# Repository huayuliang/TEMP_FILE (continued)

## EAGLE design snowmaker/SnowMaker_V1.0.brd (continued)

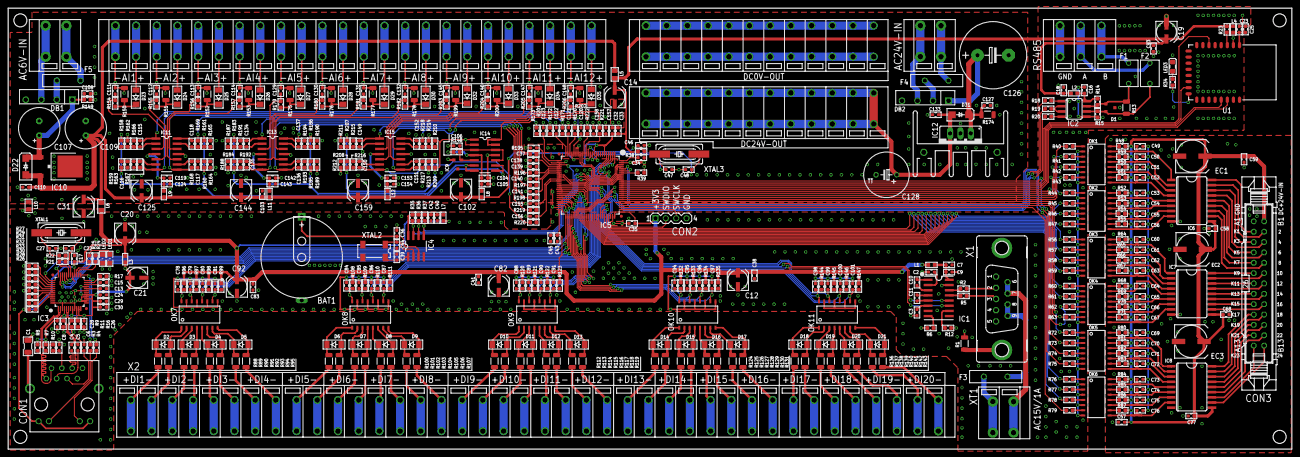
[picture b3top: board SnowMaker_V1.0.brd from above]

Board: 2 copper layers, 315.0 x 108.2 mm, 571 parts (0 on the bottom side), 406 nets.

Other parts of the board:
U$1: SNOWMAKER_V1_OUTLINE

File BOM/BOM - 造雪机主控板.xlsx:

| 造雪机主控板 |  |  |  | 编制 | 花玉良 |  | 产品编号
 |  |  |  |  | 版本 | V1 |  | 产品名称
 |  |  |  |  | 日期 | 43020 |  | 产品型号 | SMMB
 |  |  |  |  | 客户
内部编号 | 零件名称 | 元件代号 | 型号、规格 | 封装 | 数量 | 单位 | 品牌 | 单价 | 备注
焊接物料 |  |  |  |  | 1 | 套
 | 表贴元件
 | 贴片多层陶瓷电容 | C1 | 1nF/2kV | C1206 | 1 | 个
 | 贴片多层陶瓷电容 | C4、C5 | 6.8nF/50V | C0603 | 2 | 个
 | 贴片多层陶瓷电容 | C8 | 22nF/50V | C0603 | 1 | 个
 | 贴片多层陶瓷电容 | C39、C44 | 6.8pF/50V/NP0 | C0603 | 2 | 个
 | 贴片多层陶瓷电容 | C27、C22、C47、C48 | 18pF/50V/NP0 | C0603 | 4 | 个
 | 贴片多层陶瓷电容 | C115、C116、C117、C118、C134、C135、C136、C137、C149、C150、C151、C152 | 30pF/50V | C0603 | 12 | 个
 | 贴片多层陶瓷电容 | C120、C121、C122、C123、C138、C139、C140、C141、C155、C156、C157、C158 | 1nF/50V | C0603 | 12 | 个
 | 贴片多层陶瓷电容 | C6、C15、C49、C50、C51、C52、C53、C54、C55、C56、C60、C61、C62、C63、C64、C65、C66、C67、C69、C70、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 | 10nF/50V | C0603 | 49 | 个
 | 贴片多层陶瓷电容 | C2、C3、C9、C10、C11、C16、C17、C18、C24、C25、C26、C28、C29、C32、C33、C34、C35、C36、C37、C38、C4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 | 100nF/50V | C0603 | 51 | 个
 | 贴片多层陶瓷电容 | C13 | 4.7uF/10V | C0603 | 1 | 个
 | 贴片多层陶瓷电容 | C7、C23、C30、C42、C105、C124、C154、C143 | 10uF/16V | C0603 | 8 | 个
 | 贴片铝电解 5X5 | C102、C144、C159、C125 | 47uF/6.3V 5x5.8 | UD-5X5,8_NICHICON | 4 | 个
 | 贴片铝电解 5X5 | C14、C12、C19、C20、C21、C31、C82、C92 | 100uF/6.3V 5x5.8 | UD-5X5,8_NICHICON | 8 | 个
 | 贴片铝电解 8X10 | EC1、EC2、EC3 | 220uF/50V | UD-8X10_NICHICON | 3 | 个
 | 贴片电阻 | R1、R18、R19、R20、R22 | 0R | R1206 | 5 | 个
 | 贴片电阻 | R10 | 10R | R0603 | 1 | 个
 | 贴片电阻 | R2、R5 | 22R | R0603 | 2 | 个
 | 贴片电阻 | R7、R8、R9、R11 | 49R9 | R0603 | 4 | 个
 | 贴片电阻 | R14、R15 | 2.4k | R0603 | 2 | 个
 | 贴片电阻 | R16 | 12.4k/1% | R0603 | 1 | 个
 | 贴片电阻 | R21 | 1M | R0603 | 1 | 个
 | 贴片电阻 | R3、R4、R24、R25、R40、R41、R42、R43、R44、R45、R46、R47、R56、R57、R58、R59、R60、R61、R62、R63、R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 | 330R | R0603 | 11 | 个
 | 贴片电阻 | R34、R170、R171、R172、R173、R195、R196、R197、R198、R219、R220、R221、R222 | 1k | R0603 | 13 | 个
 | 贴片电阻 | R88、R89、R90、R91、R92、R93、R94、R95、R100、R101、R102、R103、R104、R105、R106、R107、R112、R1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 | 2.2k | R1206 | 40 | 个
 | 贴片电阻 | R6、R17、R12、R23、R26、R27、R28、R29、R30、R31、R32、R33、R35、R36、R37、R38、R39、R96、R97、R98、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 | 10k | R0603 | 51 | 个
 | 贴片电阻 | R48、R49、R50、R51、R52、R53、R54、R55、R64、R65、R66、R67、R68、R69、R70、R71、R80、R81、R82、R83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 | 20K | R0603 | 25 | 个
 | 贴片电阻 | R13 | 120R | R1206 | 1 | 个
 | 贴片电阻 | R150、R151、R152、R153、R175、R176、R177、R178、R199、R200、R201、R202 | 120R/0.1% | R1206 | 12 | 个
 | 贴片电阻 | R158、R159、R160、R161、R183、R184、R185、R186、R207、R208、R209、R210 | 5.11k/1% | R0603 | 12 | 个
 | 贴片电阻 | R166、R167、R168、R169、R191、R192、R193、R194、R215、R216、R217、R218 | 1k/1% | R0603 | 12 | 个
 | 贴片电阻 | R162、R163、R164、R165、R187、R188、R189、R190、R211、R212、R213、R214 | 124k/1% | R0603 | 12 | 个
 | 贴片磁珠 | L1、L2、L3、L4、L7 | 600R/100MHz | L0603 | 5 | 个
 | 贴片磁珠 | L5、L6、L10 | 100R/100MHz | L0805 | 3 | 个
 | 贴片电感 | L8、L9、L11、L12 | 10uH | L0603 | 4 | 个
 | 0805 贴片 LED | LED1 | 红色 0805 LED | LED0805 | 1 | 个
 |  | LED2、LED3 | 绿色 0805 LED | LED0805 | 2 | 个
 | 晶振 | XTAL1 | 25MHz | SM49 | 1 | 个
 | 晶振 | XTAL2 | MC-306 32.768000kHz 12.5 +20.0-20.0 | MC306 | 1 | 个
 | 晶振 | XTAL3 | 8MHz | SM49 | 1 | 个
 | TVS 管 | D1 | SM712-02H | SOT23-3 | 1 | 个
 | 开关二极管 | D2、D3、D4、D5、D6、D7、D8、D9、D10、D11、D12、D13、D14、D15、D16、D17、D18、D19、D20、D21、D23、D24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 | 1N4148 | MINI_MELF(LL-34) | 32 | 个
 | 整流二极管 | D22、D31 | 1N4007 | SMA-DO214AC | 2 | 个
 | 贴片整流桥 | DB2 | KBP2005G | KBP2005 | 1 | 个
 | 四通道光耦 | OK1、OK2、OK3、OK4、OK5、OK6、OK7、OK8、OK9、OK10、OK11 | TLP283-4 | MINI-FLAT-16 | 11 | 个
 | RS232 收发 IC | IC1 | ST3232BD | SO16 | 1 | 个
 | RS485 收发 IC | IC2 | ST3485EBD | SO08 | 1 | 个
 | 以太网 IC | IC3 | W5500 | LQFP48_7X7_0.5P | 1 | 个
 | 实时时钟 IC | IC4 | SD2068 | SOIC-8 | 1 | 个
 | MCU | IC5 | STM32F103VCT6 | LQFP100_14X14MM | 1 | 个
 | 多路达林顿驱动IC | IC6、IC7、IC8 | ULN2803 | SO18W | 3 | 个
 | 基准电压源IC | IC9 | LM4040AIM3X-2.5 | SOT23-3 | 1 | 个
 | 3.3V稳压IC | IC10 | LM1117IDTX-3.3 | TO-252/DPAK | 1 | 个
 | R2R 四运放 | IC11、IC13、IC14、IC15 | SGM8584XS14 | SOIC-14 | 4 | 个
 | 蓝牙模块 | U1 | LQ-BTM2540 | LQ-BTM2540 | 1 | 个 | 蓝讯科技
 |  |  |  |  |  | 个
 | 直插元件
 | 24V 线性稳压IC | IC12 | LM78M24 | TO-220 | 1 | 个
 | 直插铝电解电容 | C109 | 220uF/16V_M10*16 | E3 | 1 | 个
 | 直插铝电解电容 | C107 | 1000uF/16V_M10*16 | E3 | 1 | 个
 | 直插铝电解电容 | C128 | 1000uF/35V_M10*16 | E3 | 1 | 个
 | 直插铝电解电容 | C126 | 2200uF/50V_M16*25 | E7 | 1 | 个
 | 120mA PPTC 保险丝 | F1、F2 | TRF250-120T |  | 2 | 个
 | 1A PPTC 保险丝 | F3、F4、F5 | RXEF110 |  | 3 | 个
 | TO-220 散热器（含螺丝） | HS1 | 23mm * 16.5mm * 30mm |  | 1 | 套
 | 电池 | BAT1 | CR2032/1HF | CR2032-HF | 1 | 个
 | 带变压器 RJ45 座 | CON1 | HR951180A |  | 1 | 个
 | 4Pin 排针 | CON2 | 4Pin 2.54mm 单排针 | PH2.54-4P | 1 | 个
 | 26Pin 牛角座 | CON3 | 26Pin 牛角座 | 26V | 1 | 个
 | DB9 母座 | X1 | SUB-D 母座 9P 180度 | F09VP | 1 | 个
 | 2Pin 绿色弹簧端子 | XT1、XT3、XT4 | FFKDS/V1-5.08-2 | FFKDS/V1-5.08-2 | 3 | 个
 | 2Pin 绿色弹簧端子 | XT2 | FFKDS/V1-5.08-3 | FFKDS/V1-5.08-3 | 1 | 个
 | 2Pin 绿色弹簧端子 |  | FFKDS/V1-5.08-24 | FFKDS/V1-5.08-24 | 1 | 个
 | 2Pin 绿色弹簧端子 |  | FFKDS/V1-5.08-12 | FFKDS/V1-5.08-12 | 2 | 个
 | 2Pin 绿色弹簧端子 |  | FFKDS/V1-5.08-40 | FFKDS/V1-5.08-40 | 1 | 个
组装物料 |  |  |  |  | 1 | 套
 | PCB | SMMB | 315mm*100mm |  | 1 | 个
70607030 | 自攻螺丝 |  | M3X16 |  | 3 | 个
70105006 | 绿色底板 |  | 宽度108.2mm 长315-2-2mm |  | 0.311 | 米
70608009 | 挡片(左) |  | 宽度108.2mm |  | 1 | 个
70608010 | 挡片(右) |  | 宽度108.2mm |  | 1 | 个
 | 控制变压器（需定制） |  | 输入电压：220V/380V；输出：绕组 1：5V/1A；绕组 2：24V/1.2A；绕组3：12V/1.2A |  | 1 | 个
 | 蓝牙天线及转接线 |  |  |  | 1 | 套 | 蓝讯科技
指定蓝讯科技
蓝牙模块链接：https://item.taobao.com/item.htm?spm=a1z10.3-c.w4002-1228054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
蓝牙天线及转接线链接：https://item.taobao.com/item.htm?spm=2013.1.0.0.412946db8S2J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
变压器不限厂家
变压器定制链接：https://item.taobao.com/item.htm?spm=a1z0d.7625083.199830226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

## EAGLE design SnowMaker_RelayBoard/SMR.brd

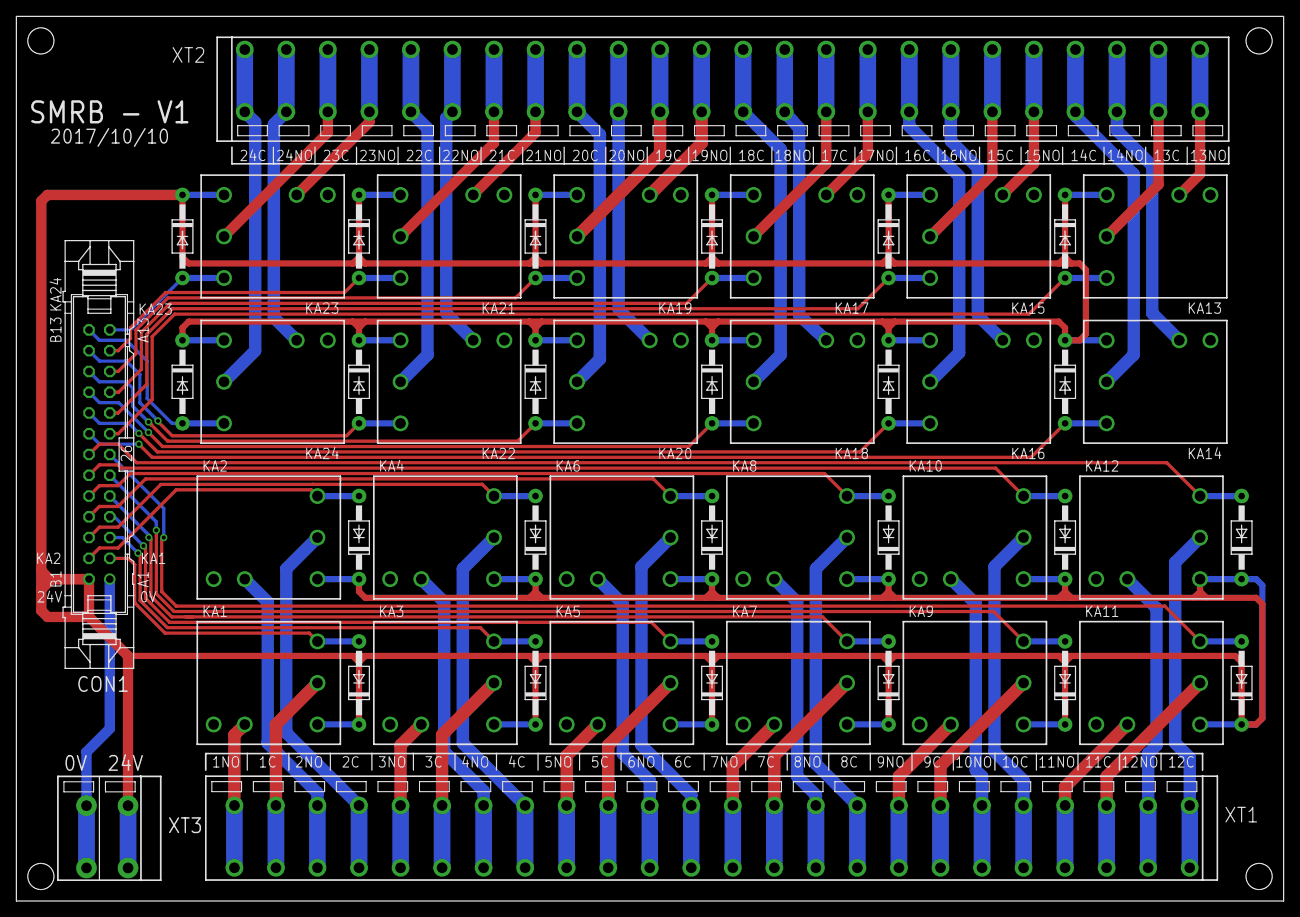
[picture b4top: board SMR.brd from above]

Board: 2 copper layers, 155.0 x 108.2 mm, 54 parts (0 on the bottom side), 74 nets.

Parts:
CON1: CON-HARTING-26V; 26V
D1, D2, D3, D4, D5, D6, D7, D8, D9, D10, D11, D12, D13, D14, D15, D16, D17, D18, D19, D20, D21, D22, D23, D24: 1N4007; DO41-10
KA1, KA2, KA3, KA4, KA5, KA6, KA7, KA8, KA9, KA10, KA11, KA12, KA13, KA14, KA15, KA16, KA17, KA18, KA19, KA20, KA21, KA22, KA23, KA24: HFKM-024-1ZST; HFKM-1ZST
LOGO1: SY-LOGO_BOTTOM
U$1: 108.2-OUTLINE
XT1, XT2: FFKDS/V1-5.08-24
XT3: FFKDS/V1-5.08-2

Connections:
+24V: CON1.B1, D1.C, D2.C, D3.C, D4.C, D5.C, D6.C, D7.C, D8.C, D9.C, D10.C, D11.C, D12.C, D13.C, D14.C, D15.C, D16.C, D17.C, D18.C, D19.C, D20.C, D21.C, D22.C, D23.C, D24.C, KA1.1, KA2.1, KA3.1, KA4.1, KA5.1, KA6.1, KA7.1, KA8.1, KA9.1, KA10.1, KA11.1, KA12.1, KA13.1, KA14.1, KA15.1, KA16.1, KA17.1, KA18.1, KA19.1, KA20.1, KA21.1, KA22.1, KA23.1, KA24.1, XT3.2@1, XT3.2@2
GND1: CON1.A1, XT3.1@1, XT3.1@2
KA1: CON1.A2, D1.A, KA1.2
KA2: CON1.B2, D2.A, KA2.2
KA3: CON1.A3, D3.A, KA3.2
KA4: CON1.B3, D4.A, KA4.2
KA5: CON1.A4, D5.A, KA5.2
KA6: CON1.B4, D6.A, KA6.2
KA7: CON1.A5, D7.A, KA7.2
KA8: CON1.B5, D8.A, KA8.2
KA9: CON1.A6, D9.A, KA9.2
KA10: CON1.B6, D10.A, KA10.2
KA11: CON1.A7, D11.A, KA11.2
KA12: CON1.B7, D12.A, KA12.2
KA13: CON1.A8, D13.A, KA13.2
KA14: CON1.B8, D14.A, KA14.2
KA15: CON1.A9, D15.A, KA15.2
KA16: CON1.B9, D16.A, KA16.2
KA17: CON1.A10, D17.A, KA17.2
KA18: CON1.B10, D18.A, KA18.2
KA19: CON1.A11, D19.A, KA19.2
KA20: CON1.B11, D20.A, KA20.2
KA21: CON1.A12, D21.A, KA21.2
KA22: CON1.B12, D22.A, KA22.2
KA23: CON1.A13, D23.A, KA23.2
KA24: CON1.B13, D24.A, KA24.2
unnamed: KA1.4, XT1.1@2, XT1.2@2
unnamed: KA1.5, XT1.1@1, XT1.2@1
unnamed: KA3.4, XT1.1@6, XT1.2@6
unnamed: KA3.5, XT1.1@5, XT1.2@5
unnamed: KA8.5, XT1.1@15, XT1.2@15
unnamed: KA8.4, XT1.1@16, XT1.2@16
unnamed: KA7.5, XT1.1@13, XT1.2@13
unnamed: KA7.4, XT1.1@14, XT1.2@14
unnamed: KA6.5, XT1.1@11, XT1.2@11
unnamed: KA6.4, XT1.1@12, XT1.2@12
unnamed: KA5.5, XT1.1@9, XT1.2@9
unnamed: KA5.4, XT1.1@10, XT1.2@10
unnamed: KA4.5, XT1.1@7, XT1.2@7
unnamed: KA4.4, XT1.1@8, XT1.2@8
unnamed: KA2.5, XT1.1@3, XT1.2@3
unnamed: KA2.4, XT1.1@4, XT1.2@4
unnamed: KA9.4, XT1.1@18, XT1.2@18
unnamed: KA9.5, XT1.1@17, XT1.2@17
unnamed: KA16.5, XT2.1@7, XT2.2@7
unnamed: KA16.4, XT2.1@8, XT2.2@8
unnamed: KA15.5, XT2.1@5, XT2.2@5
unnamed: KA15.4, XT2.1@6, XT2.2@6
unnamed: KA14.5, XT2.1@3, XT2.2@3
unnamed: KA14.4, XT2.1@4, XT2.2@4
unnamed: KA13.5, XT2.1@1, XT2.2@1
unnamed: KA13.4, XT2.1@2, XT2.2@2
unnamed: KA12.5, XT1.1@23, XT1.2@23
unnamed: KA12.4, XT1.1@24, XT1.2@24
unnamed: KA11.5, XT1.1@21, XT1.2@21
unnamed: KA11.4, XT1.1@22, XT1.2@22
unnamed: KA10.5, XT1.1@19, XT1.2@19
unnamed: KA10.4, XT1.1@20, XT1.2@20
unnamed: KA17.4, XT2.1@10, XT2.2@10
unnamed: KA17.5, XT2.1@9, XT2.2@9
unnamed: KA24.5, XT2.1@23, XT2.2@23
unnamed: KA24.4, XT2.1@24, XT2.2@24
unnamed: KA23.5, XT2.1@21, XT2.2@21
unnamed: KA23.4, XT2.1@22, XT2.2@22
unnamed: KA22.5, XT2.1@19, XT2.2@19
unnamed: KA22.4, XT2.1@20, XT2.2@20
unnamed: KA21.5, XT2.1@17, XT2.2@17
unnamed: KA21.4, XT2.1@18, XT2.2@18
unnamed: KA20.5, XT2.1@15, XT2.2@15
unnamed: KA20.4, XT2.1@16, XT2.2@16
unnamed: KA19.5, XT2.1@13, XT2.2@13
unnamed: KA19.4, XT2.1@14, XT2.2@14
unnamed: KA18.5, XT2.1@11, XT2.2@11
unnamed: KA18.4, XT2.1@12, XT2.2@12

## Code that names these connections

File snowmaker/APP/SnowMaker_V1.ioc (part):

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Mcu.Name=STM32F103V(C-D-E)Tx
Mcu.Package=LQFP100
Mcu.UserName=STM32F103VCTx
PA0-WKUP.Signal=ADCx_IN0
PA1.Signal=ADCx_IN1
PA10.GPIOParameters=GPIO_Label
PA10.GPIO_Label=TLCMP-RX
PA10.Mode=Asynchronous
PA10.Signal=USART1_RX
PA11.GPIOParameters=GPIO_Label
PA11.GPIO_Label=DOUT22
PA11.Signal=GPIO_Output
PA12.GPIOParameters=GPIO_Label
PA12.GPIO_Label=DOUT23
PA12.Signal=GPIO_Output
PA13.Mode=Serial_Wire
PA13.Signal=SYS_JTMS-SWDIO
PA14.Mode=Serial_Wire
PA14.Signal=SYS_JTCK-SWCLK
PA15.GPIOParameters=GPIO_Label
PA15.GPIO_Label=DOUT24
PA15.Signal=GPIO_Output
PA2.Signal=ADCx_IN2
PA3.Signal=ADCx_IN3
PA4.Signal=ADCx_IN4
PA5.Signal=ADCx_IN5
PA6.Signal=ADCx_IN6
PA7.Signal=ADCx_IN7
PA8.GPIOParameters=GPIO_Label
PA8.GPIO_Label=DOUT21
PA8.Signal=GPIO_Output
PA9.GPIOParameters=GPIO_Label
PA9.GPIO_Label=TLCMP-TX
PA9.Mode=Asynchronous
PA9.Signal=USART1_TX
PB0.Signal=ADCx_IN8
PB1.Signal=ADCx_IN9
PB10.GPIOParameters=GPIO_Label
PB10.GPIO_Label=ETH_INT
PB10.Signal=GPIO_Input
PB11.GPIOParameters=GPIO_Label
PB11.GPIO_Label=ETH_RST
PB11.Signal=GPIO_Output
PB12.GPIOParameters=GPIO_Label
PB12.GPIO_Label=ETHSPI_NSS
PB12.Mode=NSS_Signal_Hard_Output
PB12.Signal=SPI2_NSS
PB13.GPIOParameters=GPIO_Label
PB13.GPIO_Label=ETHSPI_SCK
PB13.Mode=Full_Duplex_Master
PB13.Signal=SPI2_SCK
PB14.GPIOParameters=GPIO_Label
PB14.GPIO_Label=ETHSPI_MISO
PB14.Mode=Full_Duplex_Master
PB14.Signal=SPI2_MISO
PB15.GPIOParameters=GPIO_Label
PB15.GPIO_Label=ETHSPI_MOSI
PB15.Mode=Full_Duplex_Master
PB15.Signal=SPI2_MOSI
PB3.GPIOParameters=GPIO_Label
PB3.GPIO_Label=BTM-\!ATC
PB3.Signal=GPIO_Output
PB4.GPIOParameters=GPIO_Label
PB4.GPIO_Label=DOUT18
PB4.Signal=GPIO_Output
PB5.GPIOParameters=GPIO_Label
PB5.GPIO_Label=RTC-INT
PB5.Signal=GPIO_Input
PB6.GPIOParameters=GPIO_Label
PB6.GPIO_Label=RTC-SCL
PB6.Mode=I2C
PB6.Signal=I2C1_SCL
PB7.GPIOParameters=GPIO_Label
PB7.GPIO_Label=RTC-SDA
PB7.Mode=I2C
PB7.Signal=I2C1_SDA
PB8.GPIOParameters=GPIO_Label
PB8.GPIO_Label=DOUT19
PB8.Signal=GPIO_Output
PB9.GPIOParameters=GPIO_Label
PB9.GPIO_Label=DOUT20
PB9.Signal=GPIO_Output
PC0.Signal=ADCx_IN10
PC1.Signal=ADCx_IN11
PC10.GPIOParameters=GPIO_Label
PC10.GPIO_Label=DOUT15
PC10.Signal=GPIO_Output
PC11.GPIOParameters=GPIO_Label
PC11.GPIO_Label=DOUT16
PC11.Signal=GPIO_Output
PC12.GPIOParameters=GPIO_Label
PC12.GPIO_Label=DOUT17
PC12.Signal=GPIO_Output
PC13-TAMPER-RTC.Signal=GPIO_Output
PC14-OSC32_IN.Signal=GPIO_Output
PC15-OSC32_OUT.Signal=GPIO_Output
PC2.GPIOParameters=GPIO_Label
PC2.GPIO_Label=DIN17
PC2.Signal=GPIO_Input
PC3.GPIOParameters=GPIO_Label
PC3.GPIO_Label=DIN18
PC3.Signal=GPIO_Input
PC4.GPIOParameters=GPIO_Label
PC4.GPIO_Label=DIN19
PC4.Signal=GPIO_Input
PC5.GPIOParameters=GPIO_Label
PC5.GPIO_Label=DIN20
PC5.Signal=GPIO_Input
PC6.GPIOParameters=GPIO_Label
PC6.GPIO_Label=DOUT11
PC6.Signal=GPIO_Output
PC7.GPIOParameters=GPIO_Label
PC7.GPIO_Label=DOUT12
PC7.Signal=GPIO_Output
PC8.GPIOParameters=GPIO_Label
PC8.GPIO_Label=DOUT13
PC8.Signal=GPIO_Output
PC9.GPIOParameters=GPIO_Label
PC9.GPIO_Label=DOUT14
PC9.Signal=GPIO_Output
PD0.GPIOParameters=GPIO_Label
PD0.GPIO_Label=DOUT1
PD0.Signal=GPIO_Output
PD1.GPIOParameters=GPIO_Label
PD1.GPIO_Label=DOUT2
PD1.Signal=GPIO_Output
PD10.GPIOParameters=GPIO_Label
PD10.GPIO_Label=WI_RS485-R/W
PD10.Signal=GPIO_Output
PD11.GPIOParameters=GPIO_Label
PD11.GPIO_Label=DOUT6
PD11.Signal=GPIO_Output
PD12.GPIOParameters=GPIO_Label
PD12.GPIO_Label=DOUT7
PD12.Signal=GPIO_Output
PD13.GPIOParameters=GPIO_Label
PD13.GPIO_Label=DOUT8
PD13.Signal=GPIO_Output
PD14.GPIOParameters=GPIO_Label
PD14.GPIO_Label=DOUT9
PD14.Signal=GPIO_Output
PD15.GPIOParameters=GPIO_Label
PD15.GPIO_Label=DOUT10
PD15.Signal=GPIO_Output
PD2.GPIOParameters=GPIO_Label
PD2.GPIO_Label=DOUT3
PD2.Signal=GPIO_Output
PD3.GPIOParameters=GPIO_Label
PD3.GPIO_Label=DOUT4
PD3.Signal=GPIO_Output
PD4.GPIOParameters=GPIO_Label
PD4.GPIO_Label=DOUT5
PD4.Signal=GPIO_Output
PD5.GPIOParameters=GPIO_Label
PD5.GPIO_Label=BTM-TX
PD5.Mode=Asynchronous
PD5.Signal=USART2_TX
PD6.GPIOParameters=GPIO_Label
PD6.GPIO_Label=BTM-RX
PD6.Mode=Asynchronous
PD6.Signal=USART2_RX
PD7.GPIOParameters=GPIO_Label
PD7.GPIO_Label=BTM-LINK
PD7.Signal=GPIO_Input
PD8.GPIOParameters=GPIO_Label
PD8.GPIO_Label=WI_RS485-TX
PD8.Mode=Asynchronous
PD8.Signal=USART3_TX
PD9.GPIOParameters=GPIO_Label
PD9.GPIO_Label=WI_RS485-RX
PD9.Mode=Asynchronous
PD9.Signal=USART3_RX
PE0.GPIOParameters=GPIO_Label
PE0.GPIO_Label=DIN1
PE0.Signal=GPIO_Input
PE1.GPIOParameters=GPIO_Label
PE1.GPIO_Label=DIN2
PE1.Signal=GPIO_Input
PE10.GPIOParameters=GPIO_Label
PE10.GPIO_Label=DIN11
PE10.Signal=GPIO_Input
PE11.GPIOParameters=GPIO_Label
PE11.GPIO_Label=DIN12
PE11.Signal=GPIO_Input
PE12.GPIOParameters=GPIO_Label
PE12.GPIO_Label=DIN13
PE12.Signal=GPIO_Input
PE13.GPIOParameters=GPIO_Label
PE13.GPIO_Label=DIN14
PE13.Signal=GPIO_Input
PE14.GPIOParameters=GPIO_Label
PE14.GPIO_Label=DIN15
PE14.Signal=GPIO_Input
PE15.GPIOParameters=GPIO_Label
PE15.GPIO_Label=DIN16
PE15.Signal=GPIO_Input
PE2.GPIOParameters=GPIO_Label
PE2.GPIO_Label=DIN3
PE2.Signal=GPIO_Input
PE3.GPIOParameters=GPIO_Label
PE3.GPIO_Label=DIN4
PE3.Signal=GPIO_Input
PE4.GPIOParameters=GPIO_Label
PE4.GPIO_Label=DIN5
PE4.Signal=GPIO_Input
PE5.GPIOParameters=GPIO_Label
PE5.GPIO_Label=DIN6
PE5.Signal=GPIO_Input
PE6.GPIOParameters=GPIO_Label
PE6.GPIO_Label=DIN7
PE6.Signal=GPIO_Input
PE7.GPIOParameters=GPIO_Label
PE7.GPIO_Label=DIN8
PE7.Signal=GPIO_Input
PE8.GPIOParameters=GPIO_Label
PE8.GPIO_Label=DIN9
PE8.Signal=GPIO_Input
PE9.GPIOParameters=GPIO_Label
PE9.GPIO_Label=DIN10
PE9.Signal=GPIO_Input

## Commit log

2017-10-09 temp1
2017-10-10 SMRB complete
2017-10-10 PI fisrt commit
2017-10-11 PI change
2017-10-13 continue
2017-10-17 init
